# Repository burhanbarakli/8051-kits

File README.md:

# 8051 geliştirme kitleri

USB üzerinden, tarayıcıdaki bir web arayüzüyle programlanan iki 8051 geliştirme kartı.

| Klasör | İçerik |
|---|---|
| [`donanim/`](donanim/) | **STC12C5A60S2 kartı.** Bootloader çipin içinde fabrikadan gelir. Şema, KiCad projesi, JLCPCB üretim dosyaları, malzeme listesi, tedarik notları ([`tedarik.md`](donanim/tedarik.md)), 3D baskı kutusu ve 8051 MCU karşılaştırması ([`mcu-karsilastirma.md`](donanim/mcu-karsilastirma.md)) |
| [`ms51_kart/`](ms51_kart/) | **Nuvoton MS51PC0AE kartı (Rev C).** KiCad projesi, üretim dosyaları, LDROM bootloader'ı (`bootloader/`), 3D baskı kutusu ve alışveriş takip sayfası. Bkz. [`ms51_kart/BENIOKU.md`](ms51_kart/BENIOKU.md) |
| [`yukleyici/`](yukleyici/) | **Web Serial yükleyici** (Chrome/Edge). STC12 ve MS51 için, testleriyle. Bkz. [`yukleyici/BENIOKU.md`](yukleyici/BENIOKU.md) |

## Durum

- Kartlar KiCad'de tasarlandı. ERC ve DRC hatasız.
- Yükleyici ve bootloader bilgisayarda test edildi:
  - STC12 protokolü stcgal ile birebir karşılaştırıldı.
  - MS51 bootloader'ı yükleyiciye karşı uçtan uca test edildi.
- Kartlar henüz üretilmedi ve gerçek donanımda denenmedi.

## Testleri çalıştırma

```bash
(cd ms51_kart/bootloader && make host)
cd yukleyici && node --test test/*.test.mjs
```

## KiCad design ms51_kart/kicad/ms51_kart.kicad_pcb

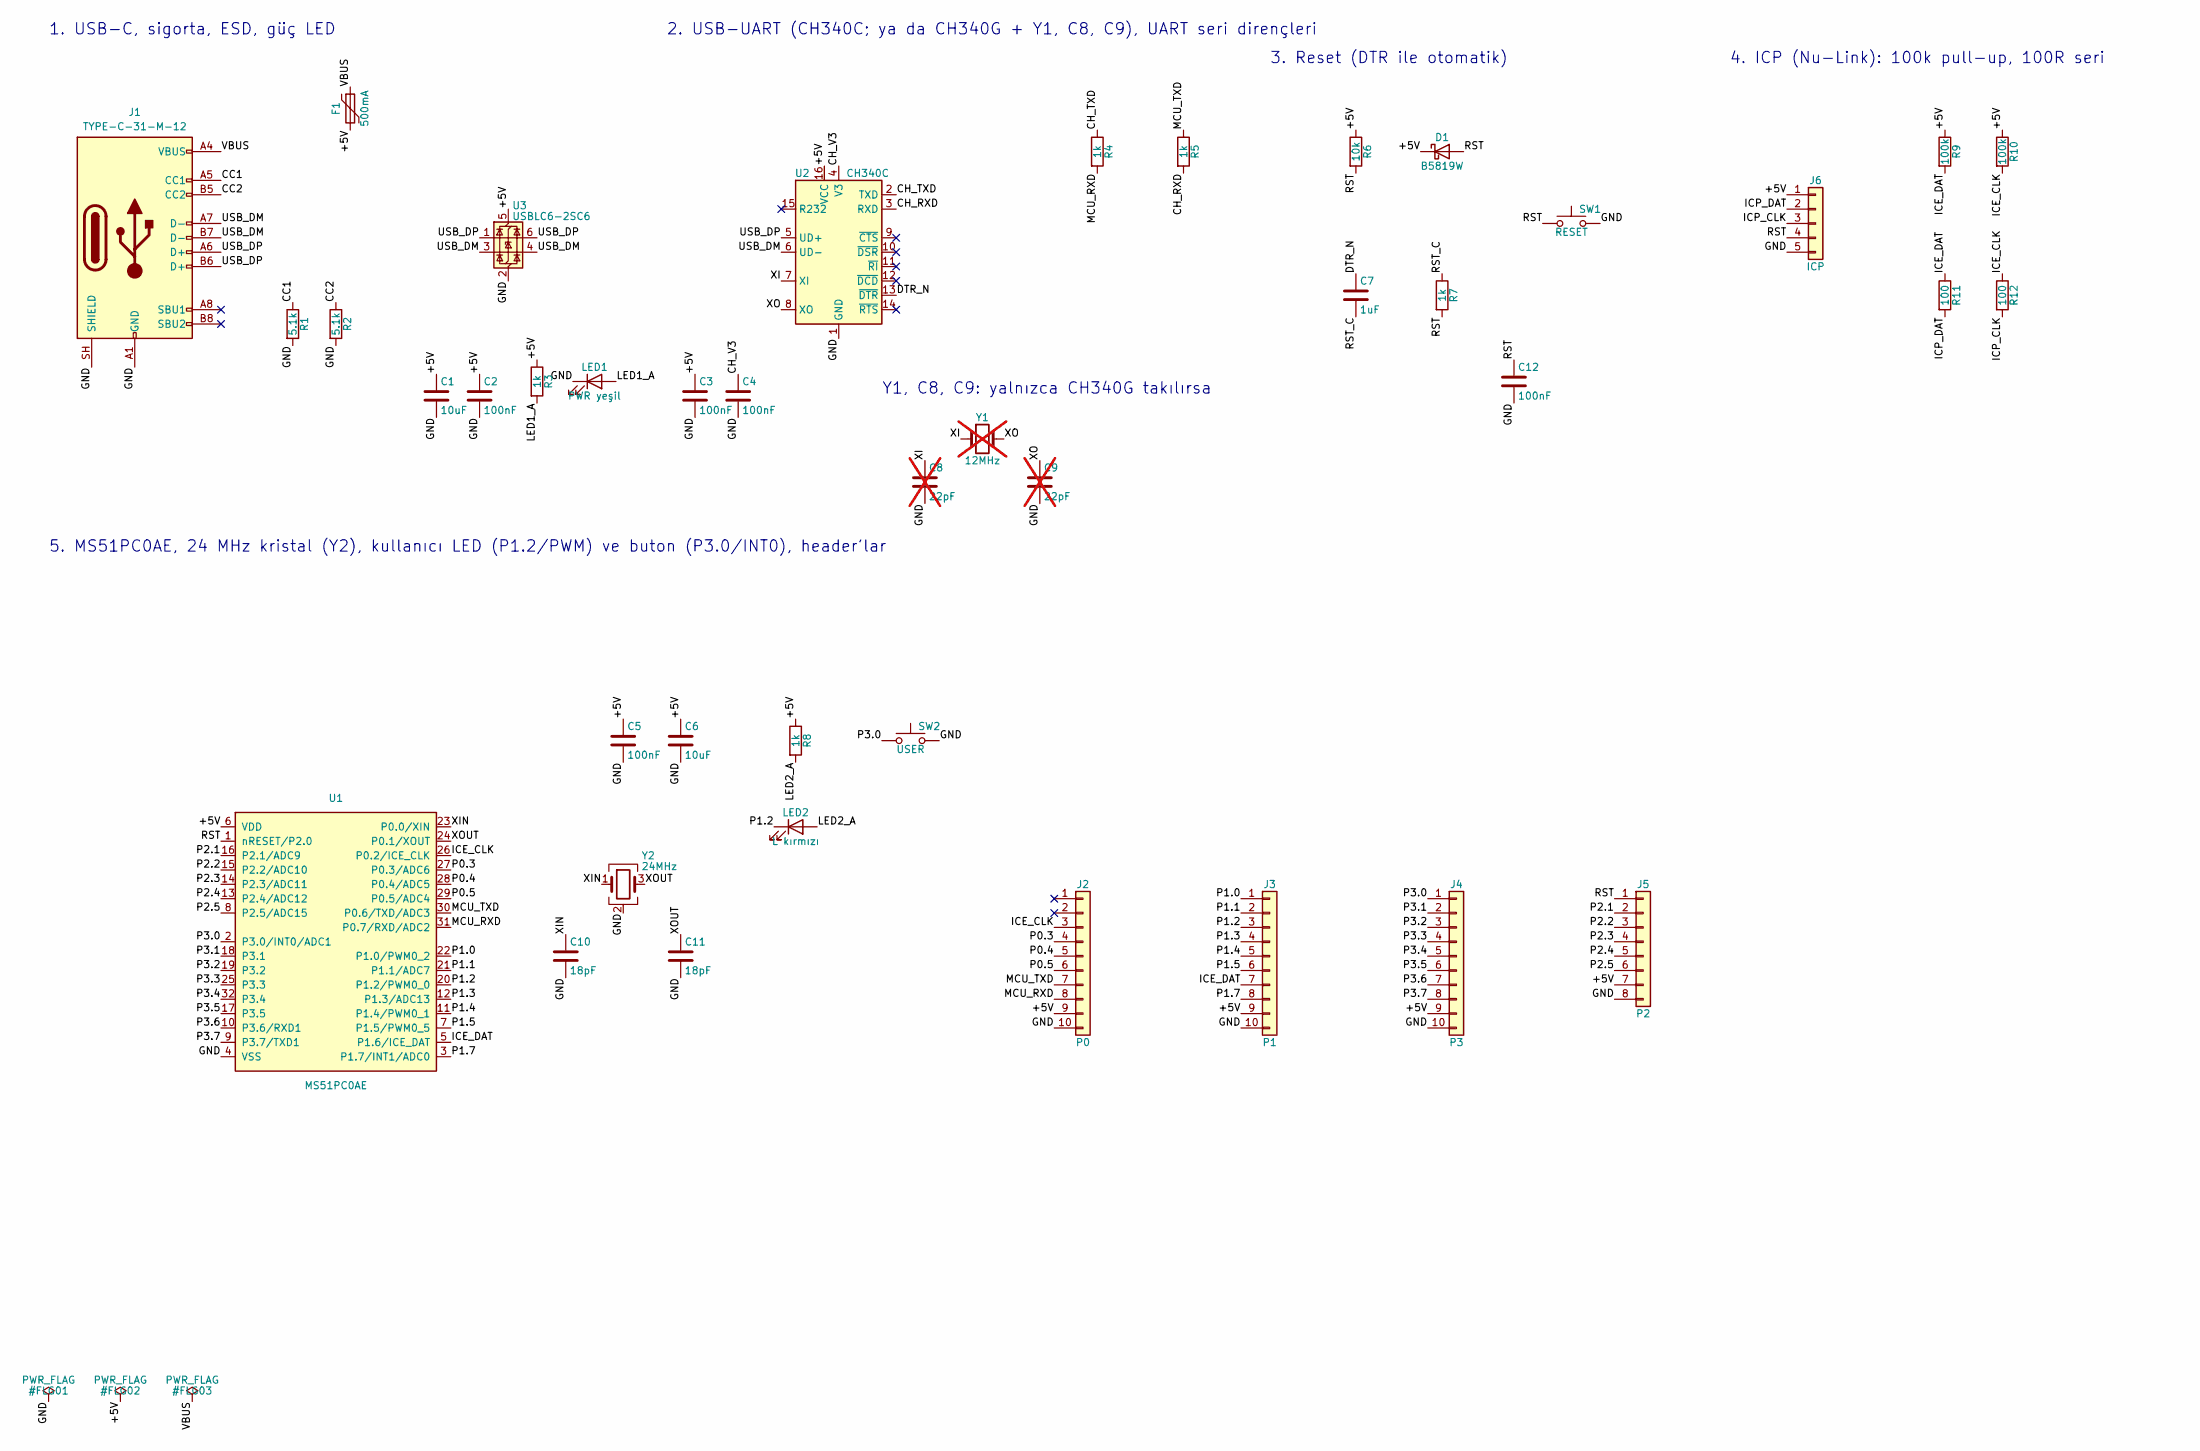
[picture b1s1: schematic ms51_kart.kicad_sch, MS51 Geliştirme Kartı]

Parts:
C1, C6: 10uF; C_0805_2012Metric; LCSC C15850
C2, C3, C4, C5, C12: 100nF; C_0603_1608Metric; LCSC C14663
C7: 1uF; C_0603_1608Metric; LCSC C15849
C8, C9: 22pF; C_0603_1608Metric; LCSC C1653; not fitted
C10, C11: 18pF; C_0603_1608Metric; LCSC C1647
D1: B5819W; D_SOD-123; LCSC C8598
F1: 500mA; Fuse_1206_3216Metric; LCSC C70075
J1: TYPE-C-31-M-12; USB_C_Receptacle_HRO_TYPE-C-31-M-12; LCSC C165948
J2: P0; PinHeader_1x10_P2.54mm_Vertical; LCSC C2337
J3: P1; PinHeader_1x10_P2.54mm_Vertical; LCSC C2337
J4: P3; PinHeader_1x10_P2.54mm_Vertical; LCSC C2337
J5: P2; PinHeader_1x08_P2.54mm_Vertical; LCSC C2337
J6: ICP; PinHeader_1x05_P2.54mm_Vertical; LCSC C2337
LED1: PWR yeşil; LED_0603_1608Metric; LCSC C72043
LED2: L kırmızı; LED_0603_1608Metric; LCSC C2286
R1, R2: 5.1k; R_0603_1608Metric; LCSC C23186
R3, R4, R5, R7, R8: 1k; R_0603_1608Metric; LCSC C21190
R6: 10k; R_0603_1608Metric; LCSC C25804
R9, R10: 100k; R_0603_1608Metric; LCSC C25803
R11, R12: 100; R_0603_1608Metric; LCSC C22775
SW1: RESET; SW_Push_1P1T_XKB_TS-1187A; LCSC C318884
SW2: USER; SW_Push_1P1T_XKB_TS-1187A; LCSC C318884
U1: MS51PC0AE; LQFP-32_7x7mm_P0.8mm; LCSC C2688383
U2: CH340C; SOIC-16_3.9x9.9mm_P1.27mm; LCSC C84681
U3: USBLC6-2SC6; SOT-23-6; LCSC C7519
Y1: 12MHz; Crystal_HC49-4H_Vertical; LCSC C16369; not fitted
Y2: 24MHz; Crystal_SMD_3225-4Pin_3.2x2.5mm; LCSC C70590

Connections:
/+5V: C1.1, C2.1, C3.1, C5.1, C6.1, D1.1 (K), F1.2, J2.9, J3.9, J4.9, J5.7, J6.1, R3.1, R6.1, R8.1, R9.1, R10.1, U1.6 (VDD), U2.16 (VCC), U3.5 (VBUS)
/CC1: J1.A5 (CC1), R1.1
/CC2: J1.B5 (CC2), R2.1
/CH_RXD: R5.2, U2.3 (RXD)
/CH_TXD: R4.1, U2.2 (TXD)
/CH_V3: C4.1, U2.4 (V3)
/DTR_N: C7.1, U2.13 (~DTR)
/GND: C1.2, C2.2, C3.2, C4.2, C5.2, C6.2, C8.2, C9.2, C10.2, C11.2, C12.2, J1.A1 (GND), J1.A12 (GND), J1.B1 (GND), J1.B12 (GND), J1.SH (SHIELD), J2.10, J3.10, J4.10, J5.8, J6.5, LED1.1 (K), R1.2, R2.2, SW1.2, SW2.2, U1.4 (VSS), U2.1 (GND), U3.2 (GND), Y2.2 (G), Y2.4 (G)
/ICE_CLK: J2.3, R10.2, R12.1, U1.26 (P0.2/ICE_CLK)
/ICE_DAT: J3.7, R9.2, R11.1, U1.5 (P1.6/ICE_DAT)
/ICP_CLK: J6.3, R12.2
/ICP_DAT: J6.2, R11.2
/LED1_A: LED1.2 (A), R3.2
/LED2_A: LED2.2 (A), R8.2
/MCU_RXD: J2.8, R4.2, U1.31 (P0.7/RXD/ADC2)
/MCU_TXD: J2.7, R5.1, U1.30 (P0.6/TXD/ADC3)
/P0.3: J2.4, U1.27 (P0.3/ADC6)
/P0.4: J2.5, U1.28 (P0.4/ADC5)
/P0.5: J2.6, U1.29 (P0.5/ADC4)
/P1.0: J3.1, U1.22 (P1.0/PWM0_2)
/P1.1: J3.2, U1.21 (P1.1/ADC7)
/P1.2: J3.3, LED2.1 (K), U1.20 (P1.2/PWM0_0)
/P1.3: J3.4, U1.12 (P1.3/ADC13)
/P1.4: J3.5, U1.11 (P1.4/PWM0_1)
/P1.5: J3.6, U1.7 (P1.5/PWM0_5)
/P1.7: J3.8, U1.3 (P1.7/INT1/ADC0)
/P2.1: J5.2, U1.16 (P2.1/ADC9)
/P2.2: J5.3, U1.15 (P2.2/ADC10)
/P2.3: J5.4, U1.14 (P2.3/ADC11)
/P2.4: J5.5, U1.13 (P2.4/ADC12)
/P2.5: J5.6, U1.8 (P2.5/ADC15)
/P3.0: J4.1, SW2.1, U1.2 (P3.0/INT0/ADC1)
/P3.1: J4.2, U1.18 (P3.1)
/P3.2: J4.3, U1.19 (P3.2)
/P3.3: J4.4, U1.25 (P3.3)
/P3.4: J4.5, U1.32 (P3.4)
/P3.5: J4.6, U1.17 (P3.5)
/P3.6: J4.7, U1.10 (P3.6/RXD1)
/P3.7: J4.8, U1.9 (P3.7/TXD1)
/RST: C12.1, D1.2 (A), J5.1, J6.4, R6.2, R7.2, SW1.1, U1.1 (nRESET/P2.0)
/RST_C: C7.2, R7.1
/USB_DM: J1.A7 (D-), J1.B7 (D-), U2.6 (UD-), U3.3 (I/O2), U3.4 (I/O2)
/USB_DP: J1.A6 (D+), J1.B6 (D+), U2.5 (UD+), U3.1 (I/O1), U3.6 (I/O1)
/VBUS: F1.1, J1.A4 (VBUS), J1.A9 (VBUS), J1.B4 (VBUS), J1.B9 (VBUS)
/XI: C8.1, U2.7 (XI), Y1.1
/XIN: C10.1, U1.23 (P0.0/XIN), Y2.1
/XO: C9.1, U2.8 (XO), Y1.2
/XOUT: C11.1, U1.24 (P0.1/XOUT), Y2.3

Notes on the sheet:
1. USB-C, sigorta, ESD, güç LED
2. USB-UART (CH340C; ya da CH340G + Y1, C8, C9), UART seri dirençleri
Y1, C8, C9: yalnızca CH340G takılırsa
3. Reset (DTR ile otomatik)
4. ICP (Nu-Link): 100k pull-up, 100R seri
5. MS51PC0AE, 24 MHz kristal (Y2), kullanıcı LED (P1.2/PWM) ve buton (P3.0/INT0), header'lar

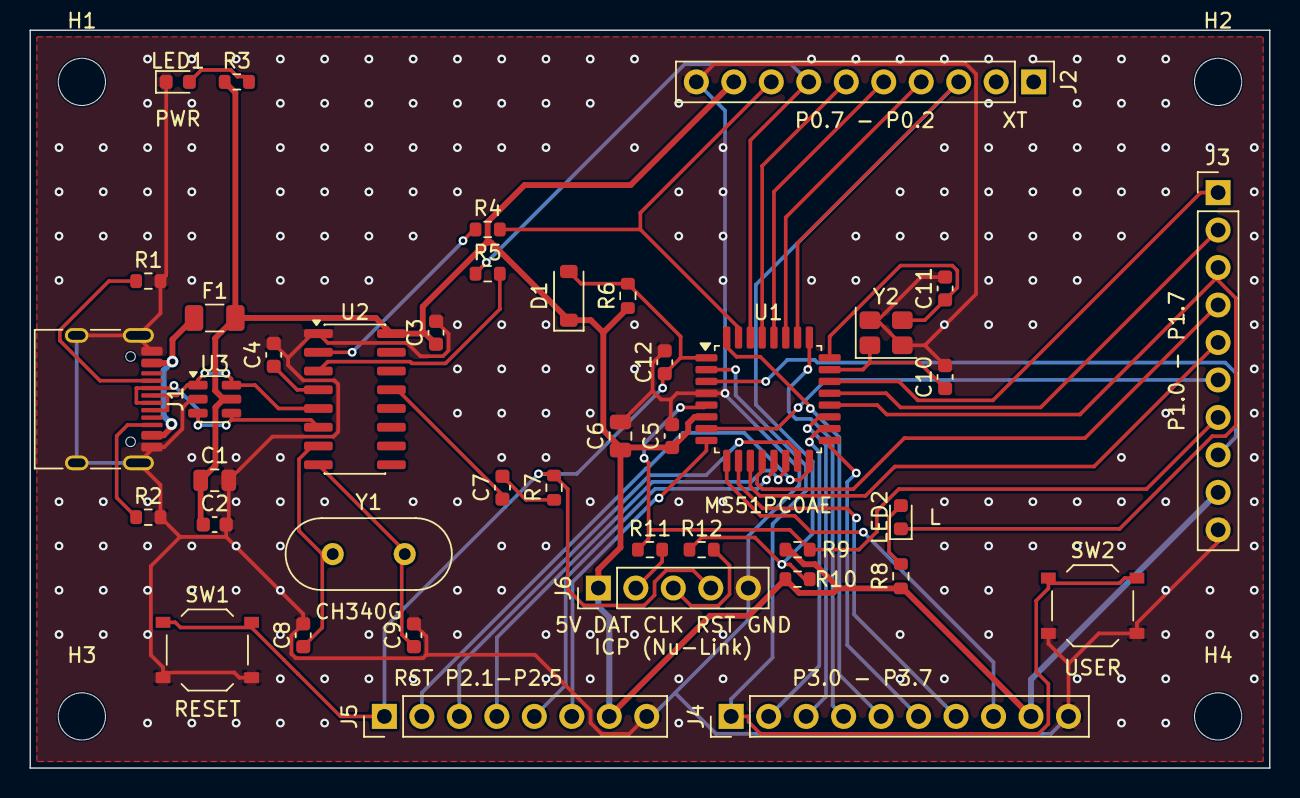
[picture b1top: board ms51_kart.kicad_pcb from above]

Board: 2 copper layers, 84.0 x 50.0 mm, 45 parts (0 on the bottom side), 48 nets.

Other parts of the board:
H1, H2, H3, H4: M3; MountingHole_3.2mm_M3

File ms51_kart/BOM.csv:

Comment,Designator,Footprint,LCSC Part #,Qty,Manufacturer Part,Aciklama
MS51PC0AE,U1,LQFP-32 7x7mm,C2688383,1,MS51PC0AE,"Nuvoton 1T 8051, 32K flash, 2K XRAM, 12-bit ADC, PWM; 24 MHz kristalle (Y2) calisir; bootloader ICP ile yuklenir"
CH340C,U2,SOP-16,C84681,1,CH340C,"USB-UART kopru, dahili osilator (kristal gerekmez). Yerine CH340G takilabilir: o zaman Y1, C8, C9 da takilir"
USBLC6-2SC6,U3,SOT-23-6,C7519,1,USBLC6-2SC6,USB D+/D- ESD koruma
TYPE-C-31-M-12,J1,USB-C 16P SMD,C165948,1,TYPE-C-31-M-12,USB-C konnektor (guc + veri)
nSMD050-16V,F1,1206,C70075,1,nSMD050-16V,"PTC sigorta, 500mA tutma"
B5819W,D1,SOD-123,C8598,1,B5819W SL,"Schottky: otomatik reset darbesinde RST'yi +5V'ta kirpar"
100nF,"C2,C3,C4,C5,C12",0603,C14663,5,CC0603KRX7R9BB104,"Dekuplaj (C2,C3,C5), CH340 V3 (C4), RST-GND (C12)"
1uF,C7,0603,C15849,1,CL10A105KB8NNNC,"DTR otomatik reset kuplaji (C12 ile birlikte RST'yi ~0,45 V'a indirir)"
10uF,"C1,C6",0805,C15850,2,CL21A106KAYNNNE,Bulk dekuplaj
5.1k,"R1,R2",0603,C23186,2,0603WAF5101T5E,USB-C CC1/CC2 pull-down (5V talebi)
10k,R6,0603,C25804,1,0603WAF1002T5E,RST pull-up
100k,"R9,R10",0603,C25803,2,0603WAF1003T5E,"ICE_DAT / ICE_CLK pull-up"
100,"R11,R12",0603,C22775,2,0603WAF1000T5E,"ICE_DAT / ICE_CLK seri direnc (ICP header tarafi)"
1k,"R3,R4,R5,R7,R8",0603,C21190,5,0603WAF1001T5E,"LED akim (R3,R8), UART seri (R4,R5), otomatik reset seri (R7)"
LED yesil,LED1,0603,C72043,1,19-217/GHC-YR1S2/3T,PWR (+5V)
LED kirmizi,LED2,0603,C2286,1,KT-0603R,"L: kullanici LED'i, P1.2 / PWM0_CH0 (aktif dusuk)"
Buton,"SW1,SW2",SMD 5.1x5.1mm,C318884,2,TS-1187A-B-A-B,"SW1=RESET, SW2=USER (P3.0/INT0)"
Pin header 1x40,"J2,J3,J4,J5,J6",2.54mm THT,C2337,2,2.54-1*40P,"Kesilerek: 3x 1x10 (P0, P1, P3) + 1x8 (P2) + 1x5 (ICP)"
12MHz,Y1,HC-49S THT,C16369,1,X49SD12MSD2SC,"TAKILMAZ: yalnizca U2 yerine CH340G takilirsa (12 MHz kristal, 20pF yuk)"
22pF,"C8,C9",0603,C1653,2,CL10C220JB8NNNC,"TAKILMAZ: yalnizca CH340G ile, kristal yuk kondansatorleri"
24MHz,Y2,SMD3225-4P,C70590,1,X322524MOB4SI,"MCU kristali: XIN (P0.0) / XOUT (P0.1), 12pF yuk, +-10ppm"
18pF,"C10,C11",0603,C1647,2,CL10C180JB8NNNC,"MCU kristali yuk kondansatorleri: 2 x (12 - ~3 pF kacak)"

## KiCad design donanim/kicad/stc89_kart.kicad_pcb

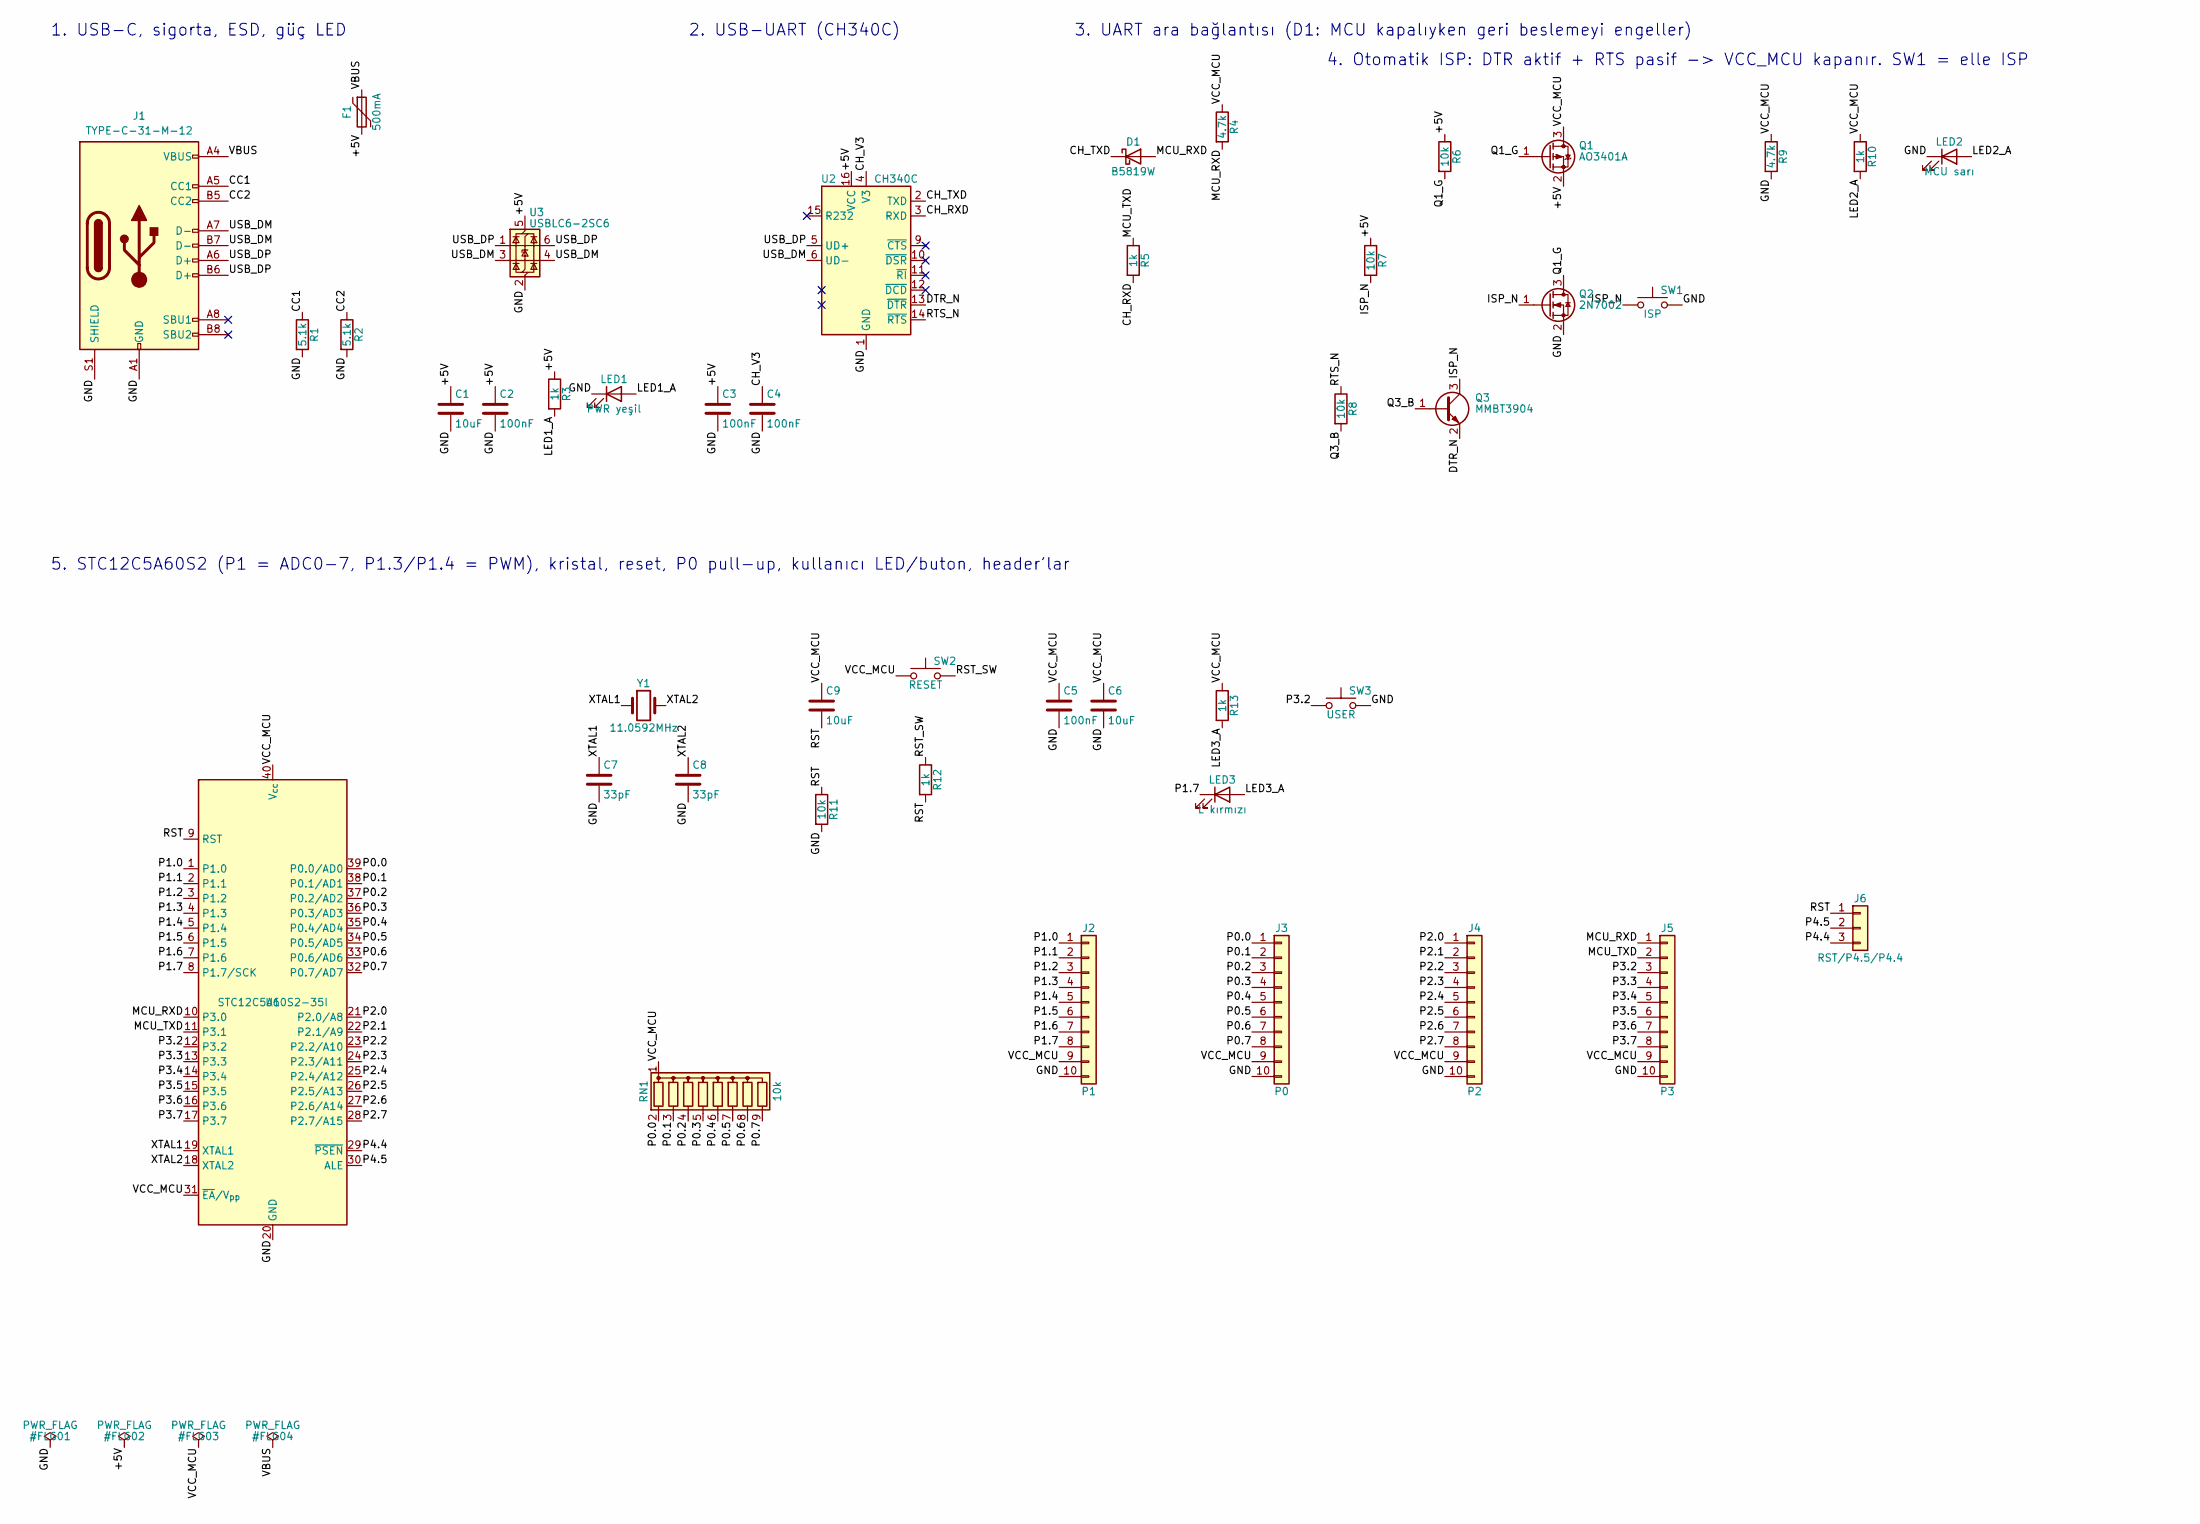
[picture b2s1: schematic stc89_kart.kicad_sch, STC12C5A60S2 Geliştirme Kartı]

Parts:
C1, C6, C9: 10uF; C_0805_2012Metric; LCSC C15850
C2, C3, C4, C5: 100nF; C_0603_1608Metric; LCSC C14663
C7, C8: 33pF; C_0603_1608Metric; LCSC C1663
D1: B5819W; D_SOD-123; LCSC C8598
F1: 500mA; Fuse_1206_3216Metric; LCSC C70075
J1: TYPE-C-31-M-12; USB_C_Receptacle_HRO_TYPE-C-31-M-12; LCSC C165948
J2: P1; PinHeader_1x10_P2.54mm_Vertical; LCSC C2337
J3: P0; PinHeader_1x10_P2.54mm_Vertical; LCSC C2337
J4: P2; PinHeader_1x10_P2.54mm_Vertical; LCSC C2337
J5: P3; PinHeader_1x10_P2.54mm_Vertical; LCSC C2337
J6: RST/P4.5/P4.4; PinHeader_1x03_P2.54mm_Vertical; LCSC C2337
LED1: PWR yeşil; LED_0603_1608Metric; LCSC C72043
LED2: MCU sarı; LED_0603_1608Metric; LCSC C72038
LED3: L kırmızı; LED_0603_1608Metric; LCSC C2286
Q1: AO3401A; SOT-23; LCSC C15127
Q2: 2N7002; SOT-23; LCSC C8545
Q3: MMBT3904; SOT-23; LCSC C20526
R1, R2: 5.1k; R_0603_1608Metric; LCSC C23186
R3, R5, R10, R12, R13: 1k; R_0603_1608Metric; LCSC C21190
R4, R9: 4.7k; R_0603_1608Metric; LCSC C23162
R6, R7, R8, R11: 10k; R_0603_1608Metric; LCSC C25804
RN1: 10k; R_Array_SIP9; LCSC C8692
SW1: ISP; SW_Push_1P1T_XKB_TS-1187A; LCSC C318884
SW2: RESET; SW_Push_1P1T_XKB_TS-1187A; LCSC C318884
SW3: USER; SW_Push_1P1T_XKB_TS-1187A; LCSC C318884
U1: STC12C5A60S2-35I; DIP-40_W15.24mm_Socket; LCSC C14550
U2: CH340C; SOIC-16_3.9x9.9mm_P1.27mm; LCSC C84681
U3: USBLC6-2SC6; SOT-23-6; LCSC C7519
Y1: 11.0592MHz; Crystal_HC49-4H_Vertical; LCSC C2203

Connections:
/+5V: C1.1, C2.1, C3.1, F1.2, Q1.2 (S), R3.1, R6.1, R7.1, U2.16 (VCC), U3.5 (VBUS)
/CC1: J1.A5 (CC1), R1.1
/CC2: J1.B5 (CC2), R2.1
/CH_RXD: R5.2, U2.3 (RXD)
/CH_TXD: D1.1 (K), U2.2 (TXD)
/CH_V3: C4.1, U2.4 (V3)
/DTR_N: Q3.2 (E), U2.13 (~DTR)
/GND: C1.2, C2.2, C3.2, C4.2, C5.2, C6.2, C7.2, C8.2, J1.A1 (GND), J1.A12 (GND), J1.B1 (GND), J1.B12 (GND), J1.S1 (SHIELD), J2.10, J3.10, J4.10, J5.10, LED1.1 (K), LED2.1 (K), Q2.2 (S), R1.2, R2.2, R9.2, R11.2, SW1.2, SW3.2, U1.20 (GND), U2.1 (GND), U3.2 (GND)
/ISP_N: Q2.1 (G), Q3.3 (C), R7.2, SW1.1
/LED1_A: LED1.2 (A), R3.2
/LED2_A: LED2.2 (A), R10.2
/LED3_A: LED3.2 (A), R13.2
/MCU_RXD: D1.2 (A), J5.1, R4.2, U1.10 (P3.0)
/MCU_TXD: J5.2, R5.1, U1.11 (P3.1)
/P0.0: J3.1, RN1.2 (R1), U1.39 (P0.0/AD0)
/P0.1: J3.2, RN1.3 (R2), U1.38 (P0.1/AD1)
/P0.2: J3.3, RN1.4 (R3), U1.37 (P0.2/AD2)
/P0.3: J3.4, RN1.5 (R4), U1.36 (P0.3/AD3)
/P0.4: J3.5, RN1.6 (R5), U1.35 (P0.4/AD4)
/P0.5: J3.6, RN1.7 (R6), U1.34 (P0.5/AD5)
/P0.6: J3.7, RN1.8 (R7), U1.33 (P0.6/AD6)
/P0.7: J3.8, RN1.9 (R8), U1.32 (P0.7/AD7)
/P1.0: J2.1, U1.1 (P1.0)
/P1.1: J2.2, U1.2 (P1.1)
/P1.2: J2.3, U1.3 (P1.2)
/P1.3: J2.4, U1.4 (P1.3)
/P1.4: J2.5, U1.5 (P1.4)
/P1.5: J2.6, U1.6 (P1.5)
/P1.6: J2.7, U1.7 (P1.6)
/P1.7: J2.8, LED3.1 (K), U1.8 (P1.7/SCK)
/P2.0: J4.1, U1.21 (P2.0/A8)
/P2.1: J4.2, U1.22 (P2.1/A9)
/P2.2: J4.3, U1.23 (P2.2/A10)
/P2.3: J4.4, U1.24 (P2.3/A11)
/P2.4: J4.5, U1.25 (P2.4/A12)
/P2.5: J4.6, U1.26 (P2.5/A13)
/P2.6: J4.7, U1.27 (P2.6/A14)
/P2.7: J4.8, U1.28 (P2.7/A15)
/P3.2: J5.3, SW3.1, U1.12 (P3.2)
/P3.3: J5.4, U1.13 (P3.3)
/P3.4: J5.5, U1.14 (P3.4)
/P3.5: J5.6, U1.15 (P3.5)
/P3.6: J5.7, U1.16 (P3.6)
/P3.7: J5.8, U1.17 (P3.7)
/P4.4: J6.3, U1.29 (~PSEN)
/P4.5: J6.2, U1.30 (ALE)
/Q1_G: Q1.1 (G), Q2.3 (D), R6.2
/Q3_B: Q3.1 (B), R8.2
/RST: C9.2, J6.1, R11.1, R12.2, U1.9 (RST)
/RST_SW: R12.1, SW2.2
/RTS_N: R8.1, U2.14 (~RTS)
/USB_DM: J1.A7 (D-), J1.B7 (D-), U2.6 (UD-), U3.3 (I/O2), U3.4 (I/O2)
/USB_DP: J1.A6 (D+), J1.B6 (D+), U2.5 (UD+), U3.1 (I/O1), U3.6 (I/O1)
/VBUS: F1.1, J1.A4 (VBUS), J1.A9 (VBUS), J1.B4 (VBUS), J1.B9 (VBUS)
/VCC_MCU: C5.1, C6.1, C9.1, J2.9, J3.9, J4.9, J5.9, Q1.3 (D), R4.1, R9.1, R10.1, R13.1, RN1.1 (common), SW2.1, U1.31 (~EA/V_{pp}), U1.40 (V_{cc})
/XTAL1: C7.1, U1.19 (XTAL1), Y1.1
/XTAL2: C8.1, U1.18 (XTAL2), Y1.2

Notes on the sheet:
1. USB-C, sigorta, ESD, güç LED
2. USB-UART (CH340C)
3. UART ara bağlantısı (D1: MCU kapalıyken geri beslemeyi engeller)
4. Otomatik ISP: DTR aktif + RTS pasif -> VCC_MCU kapanır. SW1 = elle ISP
5. STC12C5A60S2 (P1 = ADC0-7, P1.3/P1.4 = PWM), kristal, reset, P0 pull-up, kullanıcı LED/buton, header'lar

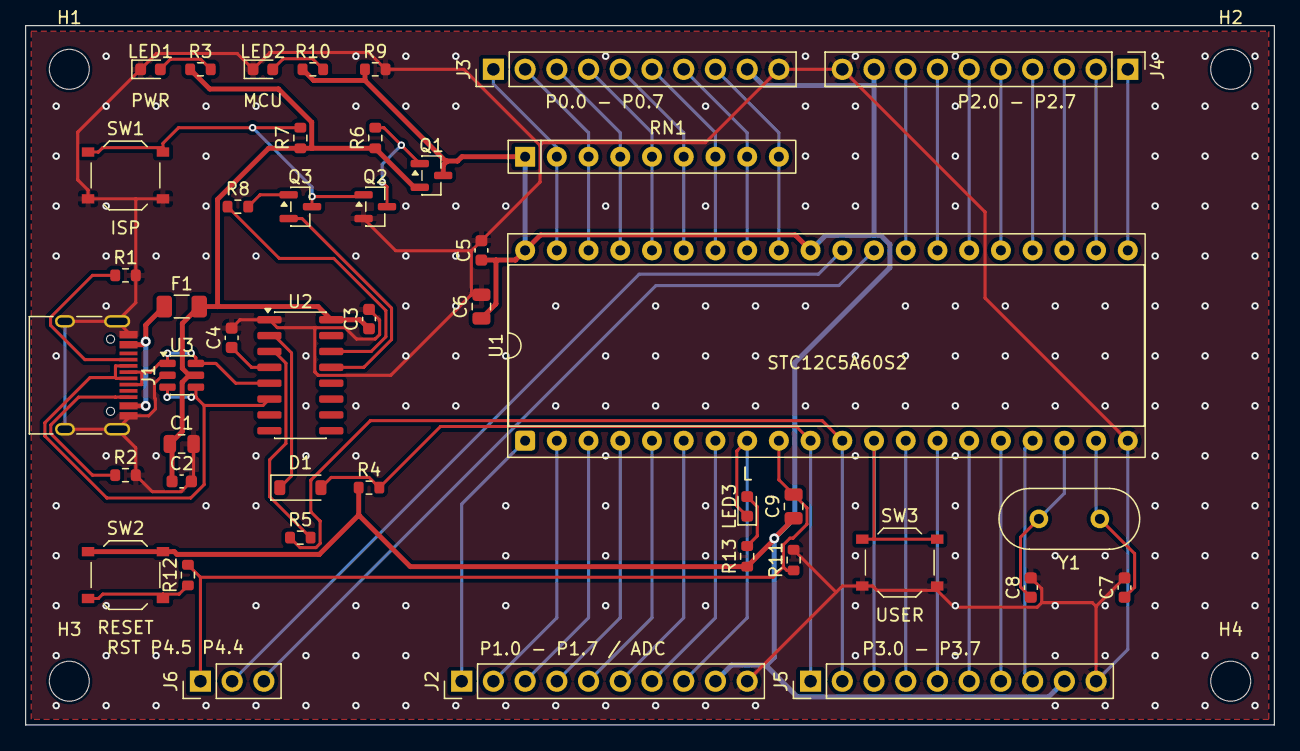
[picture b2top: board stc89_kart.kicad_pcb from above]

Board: 2 copper layers, 100.0 x 56.0 mm, 48 parts (0 on the bottom side), 57 nets.

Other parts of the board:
H1, H2, H3, H4: M3; MountingHole_3.2mm_M3

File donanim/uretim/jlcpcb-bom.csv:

Comment,Designator,Footprint,LCSC Part #
CH340C,U2,SOP-16,C84681
USBLC6-2SC6,U3,SOT-23-6,C7519
TYPE-C-31-M-12,J1,USB-C 16P SMD,C165948
nSMD050-16V,F1,1206,C70075
AO3401A,Q1,SOT-23,C15127
2N7002,Q2,SOT-23,C8545
MMBT3904,Q3,SOT-23,C20526
B5819W,D1,SOD-123,C8598
33pF,"C7,C8",0603,C1663
100nF,"C2,C3,C4,C5",0603,C14663
10uF,"C1,C6,C9",0805,C15850
5.1k,"R1,R2",0603,C23186
10k,"R6,R7,R8,R11",0603,C25804
4.7k,"R4,R9",0603,C23162
1k,"R3,R5,R10,R12,R13",0603,C21190
LED yesil,LED1,0603,C72043
LED sari,LED2,0603,C72038
LED kirmizi,LED3,0603,C2286
Buton,"SW1,SW2,SW3",SMD 5.1x5.1mm,C318884

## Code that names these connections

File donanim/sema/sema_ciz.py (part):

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tag(d, U2.RTS, 'RTS_N')
d.add(elm.NoConnect().at(U2.NC))
chain(d, -10, 7, '+5V', [elm.Capacitor().label('C3\n100nF\n(pin 16 dibine)')])
chain(d, -14, 7, 'CH_V3', [elm.Capacitor().label('C4\n100nF')])
save(d, '02-ch340c.svg')

# --------------------------------------------------------------- 3. UART ara bağlantı
d = new()
title(d, -3, 4.5, '3. UART ara bağlantısı (MCU kapalıyken geri beslemeyi engeller)')
# CH_TXD -|<|- MCU_RXD : katot CH_TXD tarafında
d.add(elm.Tag(width=TW).at((0, 0)).left().label('CH_TXD', fontsize=11))
d.add(elm.Line().at((0, 0)).right(0.6))
d1 = d.add(elm.Schottky().right().reverse().label('D1\nB5819W'))
dot = d.add(elm.Dot())
ln = d.add(elm.Line().right(1.5))
d.add(elm.Tag(width=TW).at(ln.end).right().label('MCU_RXD', fontsize=11))
r4 = d.add(elm.Resistor().at(dot.center).up().label('R4\n4.7k', loc='bottom'))
d.add(elm.Vdd().at(r4.end).label('VCC_MCU', fontsize=11))
# MCU_TXD -R5- CH_RXD
d.add(elm.Tag(width=TW).at((0, -3.5)).left().label('CH_RXD', fontsize=11))
d.add(elm.Line().at((0, -3.5)).right(0.6))
d.add(elm.Resistor().right().label('R5\n1k'))
ln = d.add(elm.Line().right(1.5 + 0.0))
d.add(elm.Tag(width=TW).at(ln.end).right().label('MCU_TXD', fontsize=11))
save(d, '03-uart.svg')

# --------------------------------------------------------------- 4. Otomatik ISP güç kesici
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d.add(elm.Line().at((q1.source[0], RAIL)).to(q1.source))
d.add(elm.Line().at(r6.end).to(q1.gate))
d.add(elm.Dot().at(r6.end))
d.add(elm.Label().at((XR6 + 0.2, r6.end[1] + 0.35)).label('Q1_G', fontsize=10, halign='left'))
dd = d.add(elm.Line().at(q1.drain).down(0.8))
d.add(elm.Tag(width=TW).at(dd.end).right().label('VCC_MCU', fontsize=11))
# Q2 N-MOSFET: drain Q1_G, kaynak GND, kapı ISP_N
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d.add(elm.Line().at(q2.gate).to(node))
d.add(elm.Line().at(r7.end).to(node))
d.add(elm.Dot().at(node))
d.add(elm.Label().at((XR7 - 0.2, node[1] + 0.35)).label('ISP_N', fontsize=10, halign='right'))
# SW1: ISP_N -> GND
d.add(elm.Dot().at((XSW, node[1])))
s1 = d.add(elm.Button().at((XSW, node[1])).down().label('SW1 ISP', loc='bottom'))
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q3 = d.add(elm.BjtNpn().theta(0).anchor('collector').at((XR7, node[1] - 1.5)).label('Q3\nMMBT3904', loc='right'))
d.add(elm.Line().at(node).to(q3.collector))
de = d.add(elm.Line().at(q3.emitter).down(0.8))
d.add(elm.Tag(width=TW).at(de.end).down().label('DTR_N', fontsize=11, rotate=True))
r8 = d.add(elm.Resistor().at(q3.base).left().label('R8\n10k'))
d.add(elm.Tag(width=TW).at(r8.end).left().label('RTS_N', fontsize=11))
d.add(elm.Label().at((-4, -3.2)).label(
    'DTR_N=L ve RTS_N=H → Q3 iletim → ISP_N=L → Q2 kesim → Q1_G=H → Q1 kesim → VCC_MCU kapalı.\n'
    'Diğer kombinasyonlarda VCC_MCU açık. SW1 basılıyken VCC_MCU kapalı (elle ISP).',
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
# Kristal
X0, Y0 = 20, 20
d.add(elm.Tag(width=TW).at((X0, Y0)).left().label('XTAL1', fontsize=11))
l1 = d.add(elm.Line().at((X0, Y0)).right(1.0))
d.add(elm.Dot())
y1 = d.add(elm.Crystal().right().label('Y1\n11.0592MHz'))
d.add(elm.Dot())
l2 = d.add(elm.Line().right(1.0))
d.add(elm.Tag(width=TW).at(l2.end).right().label('XTAL2', fontsize=11))
c7 = d.add(elm.Capacitor().at(l1.end).down().label('C7\n33pF', loc='bottom'))
d.add(elm.Ground().at(c7.end))
c8 = d.add(elm.Capacitor().at(y1.end).down().label('C8\n33pF'))
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
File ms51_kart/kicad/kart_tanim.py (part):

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CH340C ile boş bırakılır (TAKILMAZ), CH340G ile lehimlenir. CH340G Türkiye'de stokta bulunur.

Rev C (bir meslektaşın incelemesinden sonra):
  - MCU'ya 24 MHz kristal (Y2, XIN = P0.0 pin 23, XOUT = P0.1 pin 24) ve 18 pF yük
    kondansatörleri (C10, C11). Kristal 12 pF yüklü: 2 x (12 - ~3 pF kaçak) = 18 pF.
    Çip açılışta her zaman dahili HIRC ile başlar; HXT'ye yazılım geçer (CKEN/CKSWT).
    P0.0/P0.1 artık header'a çıkmaz (J2'nin 1-2. pinleri boş).
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
# Pin -> net: adı '/' öncesindeki port adı; özel görevli pinler ayrıca
MCU_PINS = {num: ad.split('/')[0] for num, (ad, *_rest) in MS51_PINLER.items()}
MCU_PINS.update({'6': '+5V', '4': 'GND', '1': 'RST', '30': 'MCU_TXD', '31': 'MCU_RXD',
                 '5': 'ICE_DAT', '26': 'ICE_CLK', '23': 'XIN', '24': 'XOUT'})


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

P0_PINS = header('P0')
P0_PINS.update({'3': 'ICE_CLK', '7': 'MCU_TXD', '8': 'MCU_RXD'})   # ICP ve UART ile ortak
del P0_PINS['1'], P0_PINS['2']                                       # P0.0/P0.1: kristal (Y2)
P1_PINS = header('P1')
P1_PINS.update({'7': 'ICE_DAT'})
P3_PINS = header('P3')
P2_PINS = {'1': 'RST', **{str(k + 1): f'P2.{k}' for k in range(1, 6)}, '7': '+5V', '8': 'GND'}

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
